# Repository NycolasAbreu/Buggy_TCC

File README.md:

# Buggy_TCC

O projeto segue as informações disponíveis em https://github.com/xtarke/automated_buggy
___
## ESP32 Pinout

### Pinos analógicos

| ESP32 pin | Analog input | Signal |
| --------- | ------------ | ------ |
| D32       | ADC0         | Bat0   |
| D33       | ADC1         | Bat1   |
| X         | ADC2         | Ampop1 |
| X         | ADC3         | Ampop2 |

### Sensor ultrassônico

| ESP32 Pin | Signal |
| --------- | ------ |
| D13       | Echo0  |
| D12       | Trig0  |
| D14       | Echo1  |
| D27       | Trig1  |

### Motores

| ESP32 Pin | Signal |
| --------- | ------ |
| D21       | PWM1   |
| D22       | PWM1N  |
| D18       | PWM2   |
| D19       | PWM2N  |

### Encoder de velocidade

| ESP32 Pin | Signal |
| --------- | ------ |
| D15       | D0     |
| D4        | D1     |

### Sensor ótico

| ESP32 Pin | Signal |
| --------- | ------ |
| D26       | R_TCRT |
| D25       | L_TCRT |

### UART

| ESP32 Pin | Signal |
| --------- | ------ |
| TX        | TX     |
| RX        | RX     |
___
## Shield projeto

___
## Exemplo de funcionamento no MicroBlocks e Bipes

- Recebe os valores dos sensores
- Caso não tenha obstáculo, seguirá em frente
- Caso tenha obstáculo na direita, se move a direita
- Caso tenha obstáculo na esquerda, se move a esquerda
- Caso tenha obstáculo em ambos os lados, para os motores

___
## Block IDEs

- https://microblocks.fun/
- http://bipes.net.br/ide/
___
## Temporário

- https://randomnerdtutorials.com/esp32-pinout-reference-gpios/

- https://www.electronicshub.org/esp32-pinout/

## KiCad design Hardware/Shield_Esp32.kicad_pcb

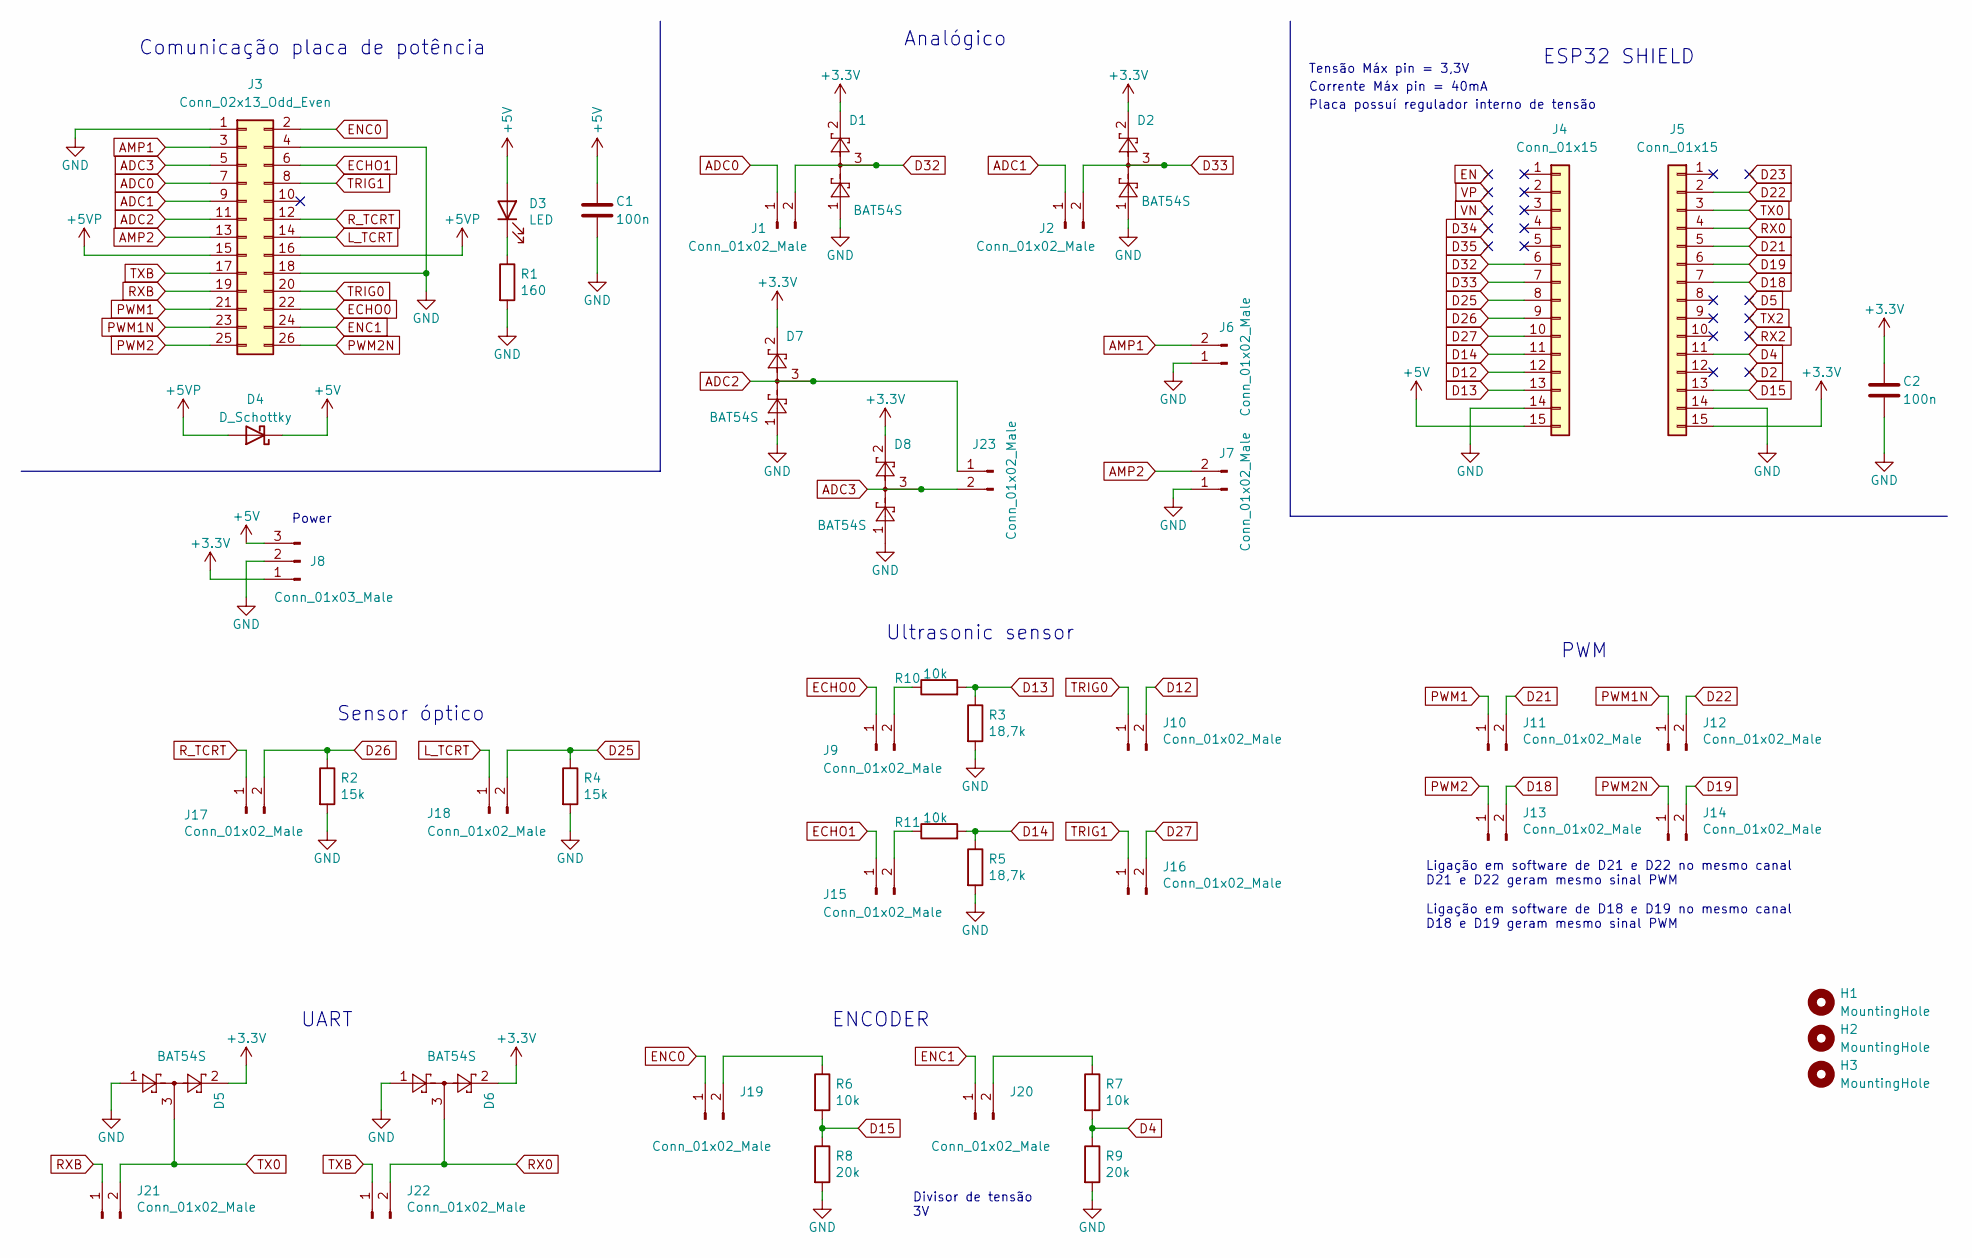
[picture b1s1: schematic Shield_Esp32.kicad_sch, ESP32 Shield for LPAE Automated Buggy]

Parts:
C1, C2: 100n; C_0805_2012Metric_Pad1.18x1.45mm_HandSolder
D1, D2, D5, D6, D7, D8: BAT54S; SOT-23
D3: LED; LED_0805_2012Metric
D4: D_Schottky; D_SMB
H1, H2, H3: MountingHole; MountingHole_2.2mm_M2
J1, J2, J6, J7, J9, J10, J11, J12, J13, J14, J15, J16, J17, J18, J19, J20, J21, J22, J23: Conn_01x02_Male; PinHeader_1x02_P2.54mm_Vertical
J3: Conn_02x13_Odd_Even; IDC-Header_2x13_P2.54mm_Vertical
J4, J5: Conn_01x15; PinSocket_1x15_P2.54mm_Vertical
J8: Conn_01x03_Male; PinHeader_1x03_P2.54mm_Vertical
R1: 160; R_0805_2012Metric
R2, R4: 15k; R_0805_2012Metric
R3, R5: 18,7k; R_0805_2012Metric
R6, R7, R10, R11: 10k; R_0805_2012Metric
R8, R9: 20k; R_0805_2012Metric

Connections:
+3.3V: C2.1, D1.2, D2.2, D5.2, D6.2, D7.2, D8.2, J5.15, J8.1
+5V: C1.1, D3.2 (A), D4.1 (K), J4.15, J8.3
+5VP: D4.2 (A), J3.15, J3.16
ADC0: J1.1, J3.7
ADC1: J2.1, J3.9
ADC2: D7.3, J3.11, J23.1
ADC3: D8.3, J3.5, J23.2
AMP1: J3.3, J6.2
AMP2: J3.13, J7.2
D4: J5.11, R7.2, R9.1
D12: J4.12, J10.2
D13: J4.13, R3.1, R10.2
D14: J4.11, R5.1, R11.2
D15: J5.13, R6.2, R8.1
D18: J5.7, J13.2
D19: J5.6, J14.2
D21: J5.5, J11.2
D22: J5.2, J12.2
D25: J4.8, J18.2, R4.1
D26: J4.9, J17.2, R2.1
D27: J4.10, J16.2
D32: D1.3, J1.2, J4.6
D33: D2.3, J2.2, J4.7
ECHO0: J3.22, J9.1
ECHO1: J3.6, J15.1
ENC0: J3.2, J19.1
ENC1: J3.24, J20.1
GND: C1.2, C2.2, D1.1, D2.1, D5.1, D6.1, D7.1, D8.1, J3.1, J3.4, J3.18, J4.14, J5.14, J6.1, J7.1, J8.2, R1.2, R2.2, R3.2, R4.2, R5.2, R8.2, R9.2
L_TCRT: J3.14, J18.1
unnamed: D3.1 (K), R1.1
unnamed: J9.2, R10.1
unnamed: J15.2, R11.1
unnamed: J19.2, R6.1
unnamed: J20.2, R7.1
PWM1: J3.21, J11.1
PWM1N: J3.23, J12.1
PWM2: J3.25, J13.1
PWM2N: J3.26, J14.1
RX0: D6.3, J5.4, J22.2
RXB: J3.19, J21.1
R_TCRT: J3.12, J17.1
TRIG0: J3.20, J10.1
TRIG1: J3.8, J16.1
TX0: D5.3, J5.3, J21.2
TXB: J3.17, J22.1

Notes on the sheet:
Analógico
Corrente Máx pin = 40mA
PWM
Sensor óptico
Divisor de tensão 3V
Ligação em software de D21 e D22 no mesmo canal D21 e D22 geram mesmo sinal PWM Ligação em software de D18 e D19 no mesmo canal D18 e D19 geram mesmo sinal PWM
UART
Power
ENCODER
Placa possuí regulador interno de tensão
Tensão Máx pin = 3,3V
Ultrasonic sensor
Comunicação placa de potência
ESP32 SHIELD

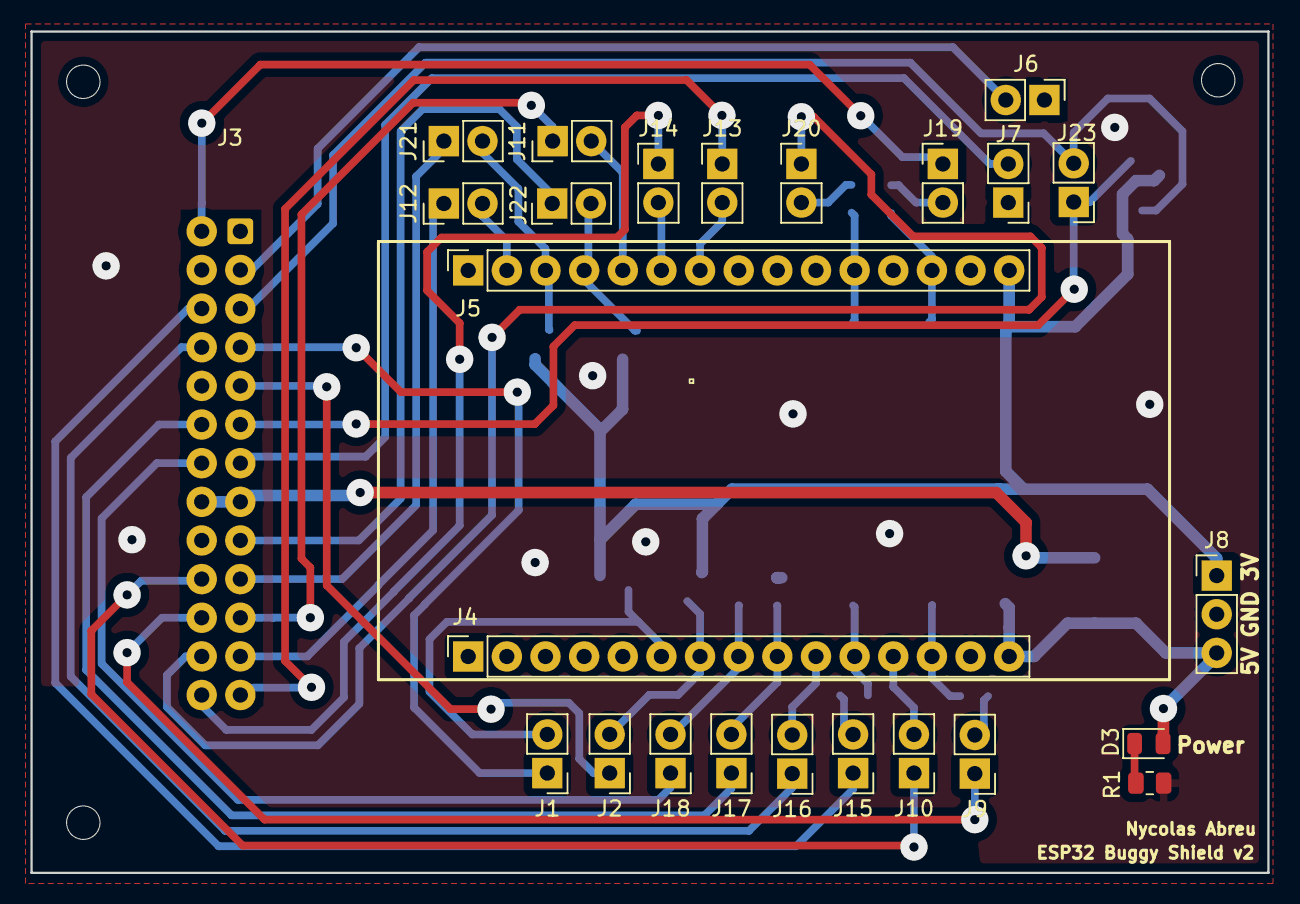
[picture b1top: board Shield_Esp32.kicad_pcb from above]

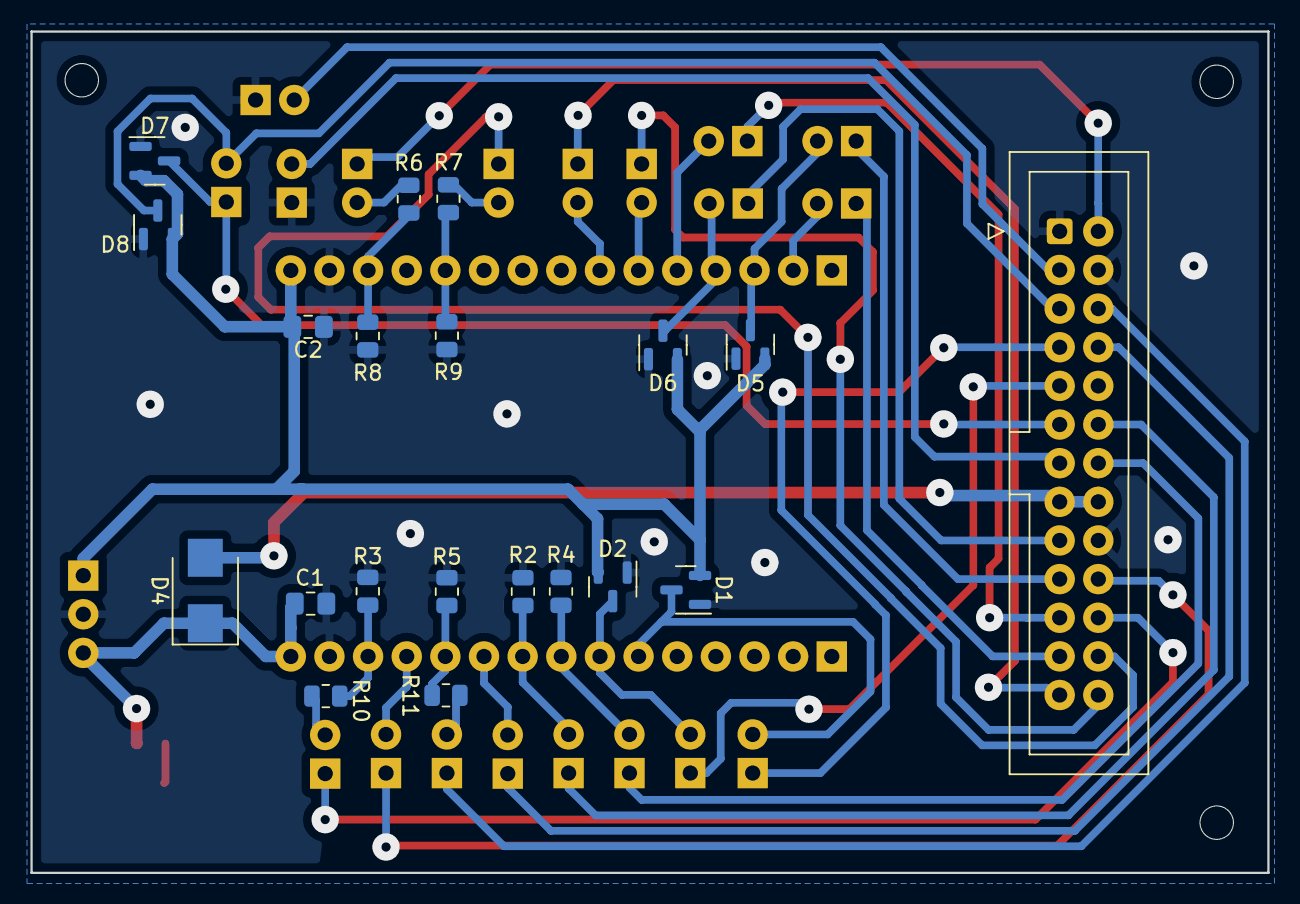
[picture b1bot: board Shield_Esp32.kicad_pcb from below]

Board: 2 copper layers, 81.3 x 55.3 mm, 47 parts (20 on the bottom side), 45 nets.

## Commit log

2022-08-24 Inicio pcb
2022-08-25 pcb att
2022-08-25 pcb update
2022-08-26 pcb update + new pcb
2022-08-26 final pcb
2022-08-29 Gerber
2022-08-30 update pcb
2022-09-08 Starting tests
2022-09-12 fixed pcb
2022-09-12 class motor
2022-09-19 update pins
2022-09-20 Sensor de linha
2022-09-21 update logic
2022-09-22 Encoder
2022-09-23 main program
2022-09-26 Microblocks functions
2022-09-28 update examples
2022-09-29 Add encoder
2022-09-30 bipes
2022-10-02 ble bipes
2022-10-03 update encoder
2022-10-05 correção pino encoder
2022-10-05 mudança pino encoder
2022-10-07 updata readme
2022-12-03 Interface ultrassom
